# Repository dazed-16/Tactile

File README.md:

# Tactile

Tactile is a custom split mechanical keyboard for programming, live coding and CAD, with a thumb touchpad for pointer control.

## Why make it?

The aim is a keyboard that feels personal and comfortable during long desk sessions. A split layout lets each hand rest at its own angle, while thumb controls reduce trips between the keyboard and mouse. Tactile switches give clear feedback, and printed keycaps and a case leave room for customization.

## How it works

A wireless controller connects to the computer over Bluetooth. A ribbon cable joins the two halves, and the controller scans the key matrix. The right thumb controls the touchpad; left-thumb keys handle mouse clicks. Layers provide the remaining keyboard functions.

## Challenges so far

Fitting the thumb keys and touchpad into a useful layout has meant balancing comfort with space for the electronics. Another challenge has been choosing a controller and expanding its pins to handle both the keyboard and pointing device. Matching component footprints and keeping the parts affordable still need attention.

The project is in the design stage. The boards and schematics are present; firmware and the physical build are still ahead.

## Design pictures

## Files

Open the left and right projects under `Tactile/PCB/` in KiCad. Custom libraries are in `Tactile/Libraries/`, and printable geometry is in `Tactile/Model/`. The purchase list is also available as [BOM.csv](BOM.csv).

Gerbers and drill files are in the [left fabrication folder](Tactile/PCB/Left%20side/fabrication/) and [right fabrication folder](Tactile/PCB/Right%20side/fabrication/), with a ZIP package for each half. These are design exports; fabrication checks are still pending.

## Purchase BOM

Submission estimate in USD, using the current supplier list and delivery to Mexico. Prices are per listed purchase unit; line totals already include quantity. **Estimated order total: $211.80** ($76.80 components + $95.00 shipping + $40.00 tax/import allowance).

| Component or charge | Buy quantity | Unit USD | Line total USD | Source |
| --- | --- | --- | --- | --- |
| BLE controller | 1 | 9.90 | 9.90 | [Part](https://www.seeedstudio.com/Seeed-XIAO-BLE-nRF52840-p-5201.html) |
| Tactile switches | 2 packs | 9.99 | 19.98 | [Part](https://en.akkogear.com/product/creamy-purple-u1-switch/) |
| Touchpad | 1 | 9.63 | 9.63 | [Part](https://www.mouser.com/en/ProductDetail/Cirque/TM040040-2024-302?qs=wd5RIQLrsJgMzmw571gvDw%3D%3D) |
| Matrix diodes | 100 | 0.0665 | 6.65 | [Part](https://www.digikey.com/en/products/detail/diodes-incorporated/1N4148W-7-F/815280) |
| Shift registers | 2 | 0.30 | 0.60 | [Part](https://www.digikey.com/en/products/detail/nexperia-usa-inc/74HC595D-118/763394) |
| Capacitors | 10 | 0.098 | 0.98 | [Part](https://www.digikey.com/en/products/detail/yageo/CC0805KRX7R9BB104/302874) |
| Touchpad connector | 1 | 2.00 | 2.00 | [Part](https://www.digikey.com/en/products/detail/hirose-electric-co-ltd/FH12-12S-0-5SH-55/1110316) |
| Touchpad cable (estimate) | 1 | 2.00 | 2.00 | [Part](https://www.digikey.com/en/products/detail/assmann-wsw-components/AFFC-050-12-051-11/6570261) |
| Ribbon cable | 2 feet | 1.79 | 3.58 | [Part](https://www.digikey.com/en/products/detail/assmann-wsw-components/AWG28-14-F-300/655738) |
| IDC sockets | 2 | 0.60 | 1.20 | [Part](https://www.digikey.com/en/products/detail/assmann-wsw-components/AWP-14-8240-T/5244612) |
| IDC strain reliefs | 2 | 0.10 | 0.20 | [Part](https://www.digikey.com/en/products/base-product/assmann-wsw-components/123/AWZ/567962) |
| IDC headers | 2 | 0.63 | 1.26 | [Part](https://www.digikey.com/en/products/detail/assmann-wsw-components/AWHW-14G-0202-T/5224931) |
| Power switch | 1 | 0.72 | 0.72 | [Part](https://www.digikey.com/en/products/detail/e-switch/EG1218/101726) |
| Battery | 1 | 9.95 | 9.95 | [Part](https://www.digikey.com/en/products/detail/adafruit-industries-llc/258/5054544) |
| USB cable | 1 | 4.95 | 4.95 | [Part](https://www.adafruit.com/product/4474) |
| Battery protection IC (estimate) | 1 | 1.00 | 1.00 | [Part](https://www.ti.com/product/BQ2970) |
| Dual MOSFET (estimate) | 1 | 1.50 | 1.50 | [Part](https://www.ti.com/product/CSD83325L) |
| 330 ohm resistor (estimate) | 1 | 0.10 | 0.10 | To select |
| 2.2 kOhm resistor (estimate) | 1 | 0.10 | 0.10 | To select |
| Battery connector (estimate) | 1 | 0.50 | 0.50 | [Part](https://www.jst-mfg.com/product/index.php?series=ACH) |
| DigiKey shipping | 1 | 30.00 | 30.00 | [Part](https://www.digikey.com.mx/en) |
| Seeed shipping (estimate) | 1 | 10.00 | 10.00 | [Part](https://support.seeedstudio.com/knowledgebase/topics/56172-shipping) |
| Akko shipping (estimate) | 1 | 15.00 | 15.00 | [Part](https://en.akkogear.com/faq/how-many-days-will-the-delivery-take-if-i-order-today/) |
| Mouser shipping (estimate) | 1 | 20.00 | 20.00 | [Part](https://www.mouser.mx/es/saleterms/) |
| Adafruit shipping (estimate) | 1 | 20.00 | 20.00 | [Part](https://www.adafruit.com/shippinginfo) |
| Tax and import charges (estimate) | 1 | 40.00 | 40.00 | [Part](https://wwwmatnp.sat.gob.mx/articulo/43379/articulo-27) |

The unquoted components and shipping use planning allowances, not supplier quotes. Shipping assumes separate orders from DigiKey, Seeed, Akko, Mouser and Adafruit. DigiKey's $30 follows its published Mexico rate below $100; the remaining shipping allowances are provisional. The $40 tax/import allowance is a budget reserve, not a tax-rate calculation or guaranteed upper bound. Final checkout and carrier charges may differ.

Verified diode price: **100 × $0.06650 = $6.65**, cut tape. Other listed component prices are earlier supplier estimates. No parts order has been placed.

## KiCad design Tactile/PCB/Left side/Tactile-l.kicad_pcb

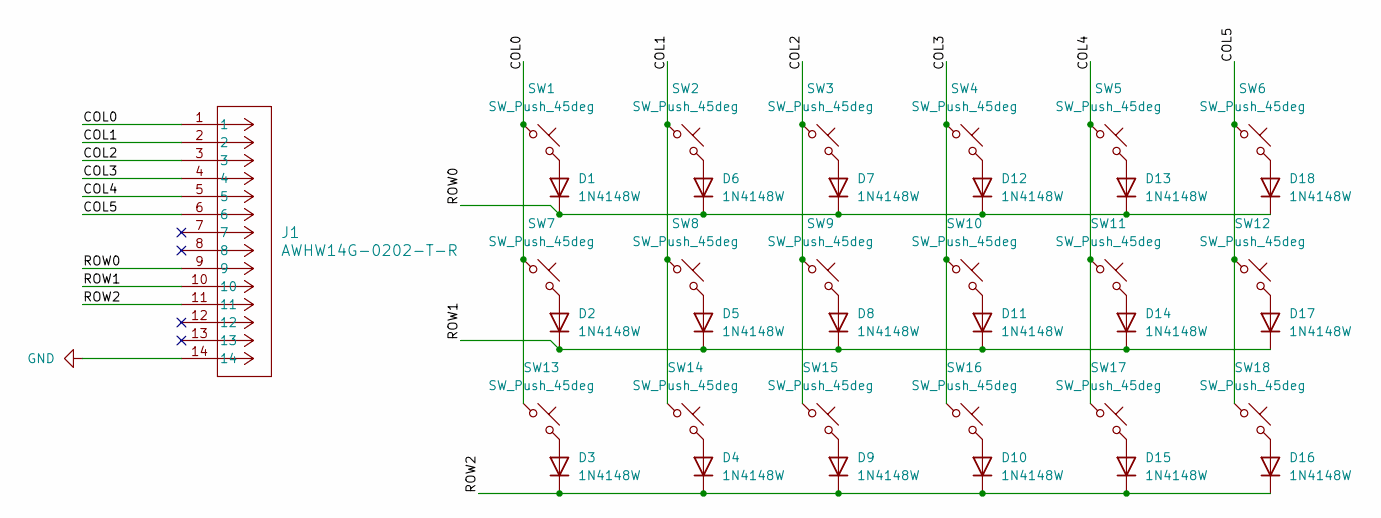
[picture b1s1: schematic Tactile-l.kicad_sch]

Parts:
D1, D2, D3, D4, D5, D6, D7, D8, D9, D10, D11, D12, D13, D14, D15, D16, D17, D18: 1N4148W; D_SOD-123
J1: AWHW14G-0202-T-R; CONN_AWHW14G-0x02-T_ASM
SW1, SW2, SW3, SW4, SW5, SW6, SW7, SW8, SW9, SW10, SW11, SW12, SW13, SW14, SW15, SW16, SW17, SW18: SW_Push_45deg; Knowles_SPH0645LM4H-6_3.5x2.65mm

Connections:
/COL0: J1.1, SW1.1, SW7.1, SW13.1
/COL1: J1.2, SW2.1, SW8.1, SW14.1
/COL2: J1.3, SW3.1, SW9.1, SW15.1
/COL3: J1.4, SW4.1, SW10.1, SW16.1
/COL4: J1.5, SW5.1, SW11.1, SW17.1
/COL5: J1.6, SW6.1, SW12.1, SW18.1
/ROW0: D1.1 (K), D6.1 (K), D7.1 (K), D12.1 (K), D13.1 (K), D18.1 (K), J1.9
/ROW1: D2.1 (K), D5.1 (K), D8.1 (K), D11.1 (K), D14.1 (K), D17.1 (K), J1.10
/ROW2: D3.1 (K), D4.1 (K), D9.1 (K), D10.1 (K), D15.1 (K), D16.1 (K), J1.11
GND: J1.14
unnamed: D1.2 (A), SW1.2
unnamed: D2.2 (A), SW7.2
unnamed: D3.2 (A), SW13.2
unnamed: D4.2 (A), SW14.2
unnamed: D5.2 (A), SW8.2
unnamed: D6.2 (A), SW2.2
unnamed: D7.2 (A), SW3.2
unnamed: D8.2 (A), SW9.2
unnamed: D9.2 (A), SW15.2
unnamed: D10.2 (A), SW16.2
unnamed: D11.2 (A), SW10.2
unnamed: D12.2 (A), SW4.2
unnamed: D13.2 (A), SW5.2
unnamed: D14.2 (A), SW11.2
unnamed: D15.2 (A), SW17.2
unnamed: D16.2 (A), SW18.2
unnamed: D17.2 (A), SW12.2
unnamed: D18.2 (A), SW6.2

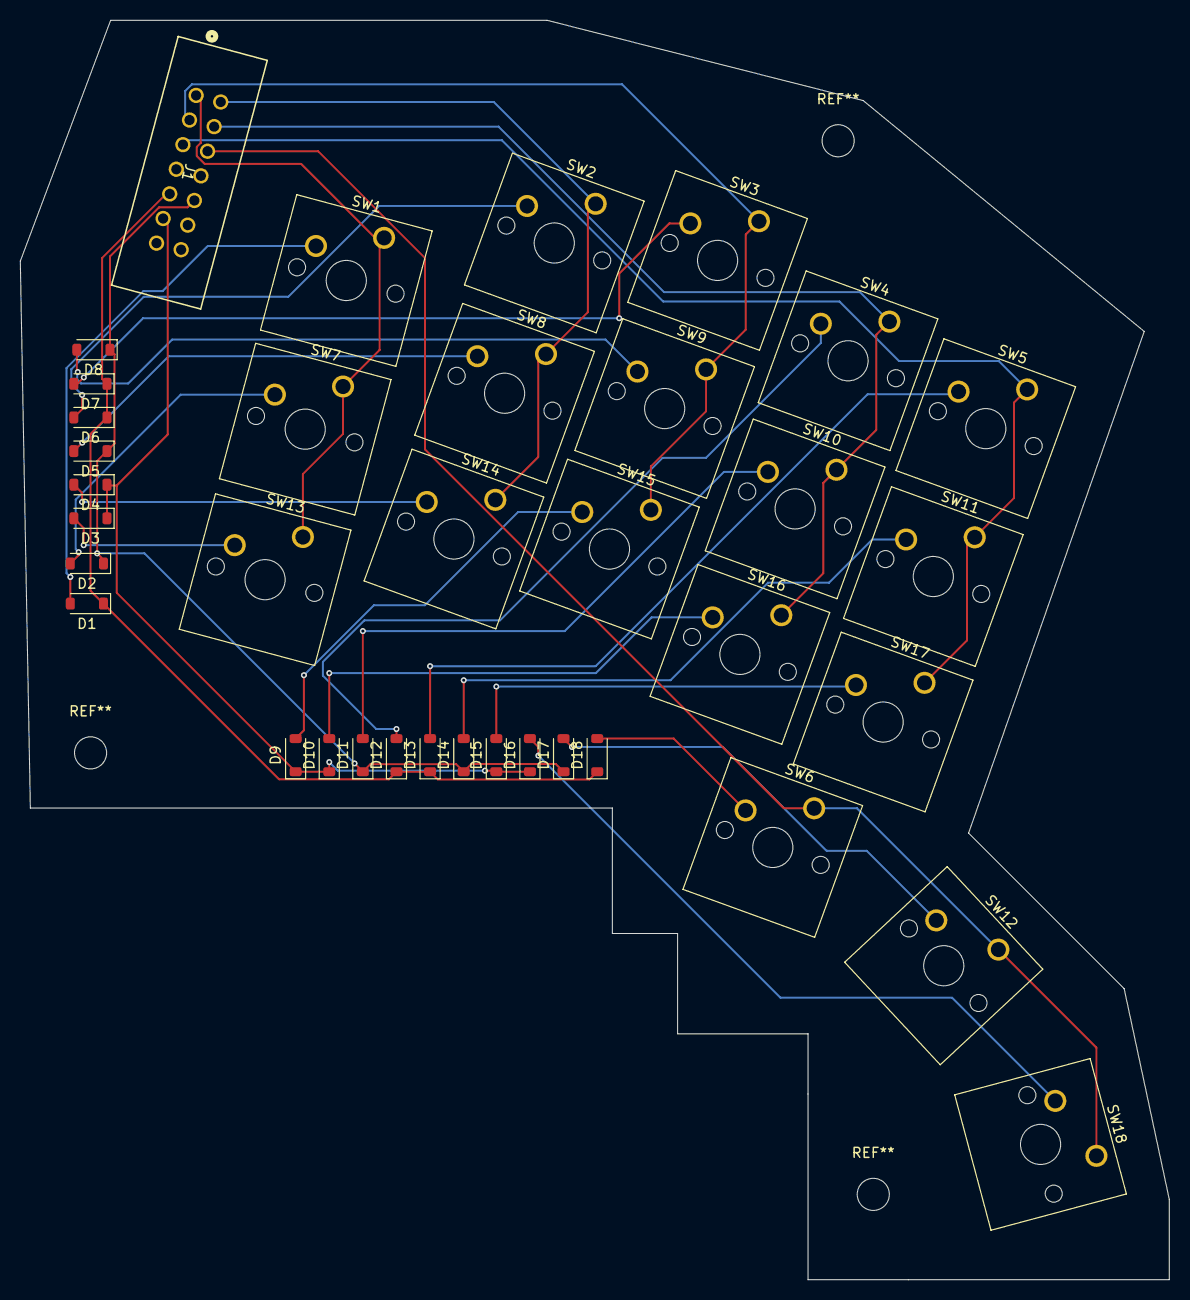
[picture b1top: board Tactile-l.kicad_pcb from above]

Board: 2 copper layers, 114.5 x 125.5 mm, 37 parts (0 on the bottom side), 27 nets.

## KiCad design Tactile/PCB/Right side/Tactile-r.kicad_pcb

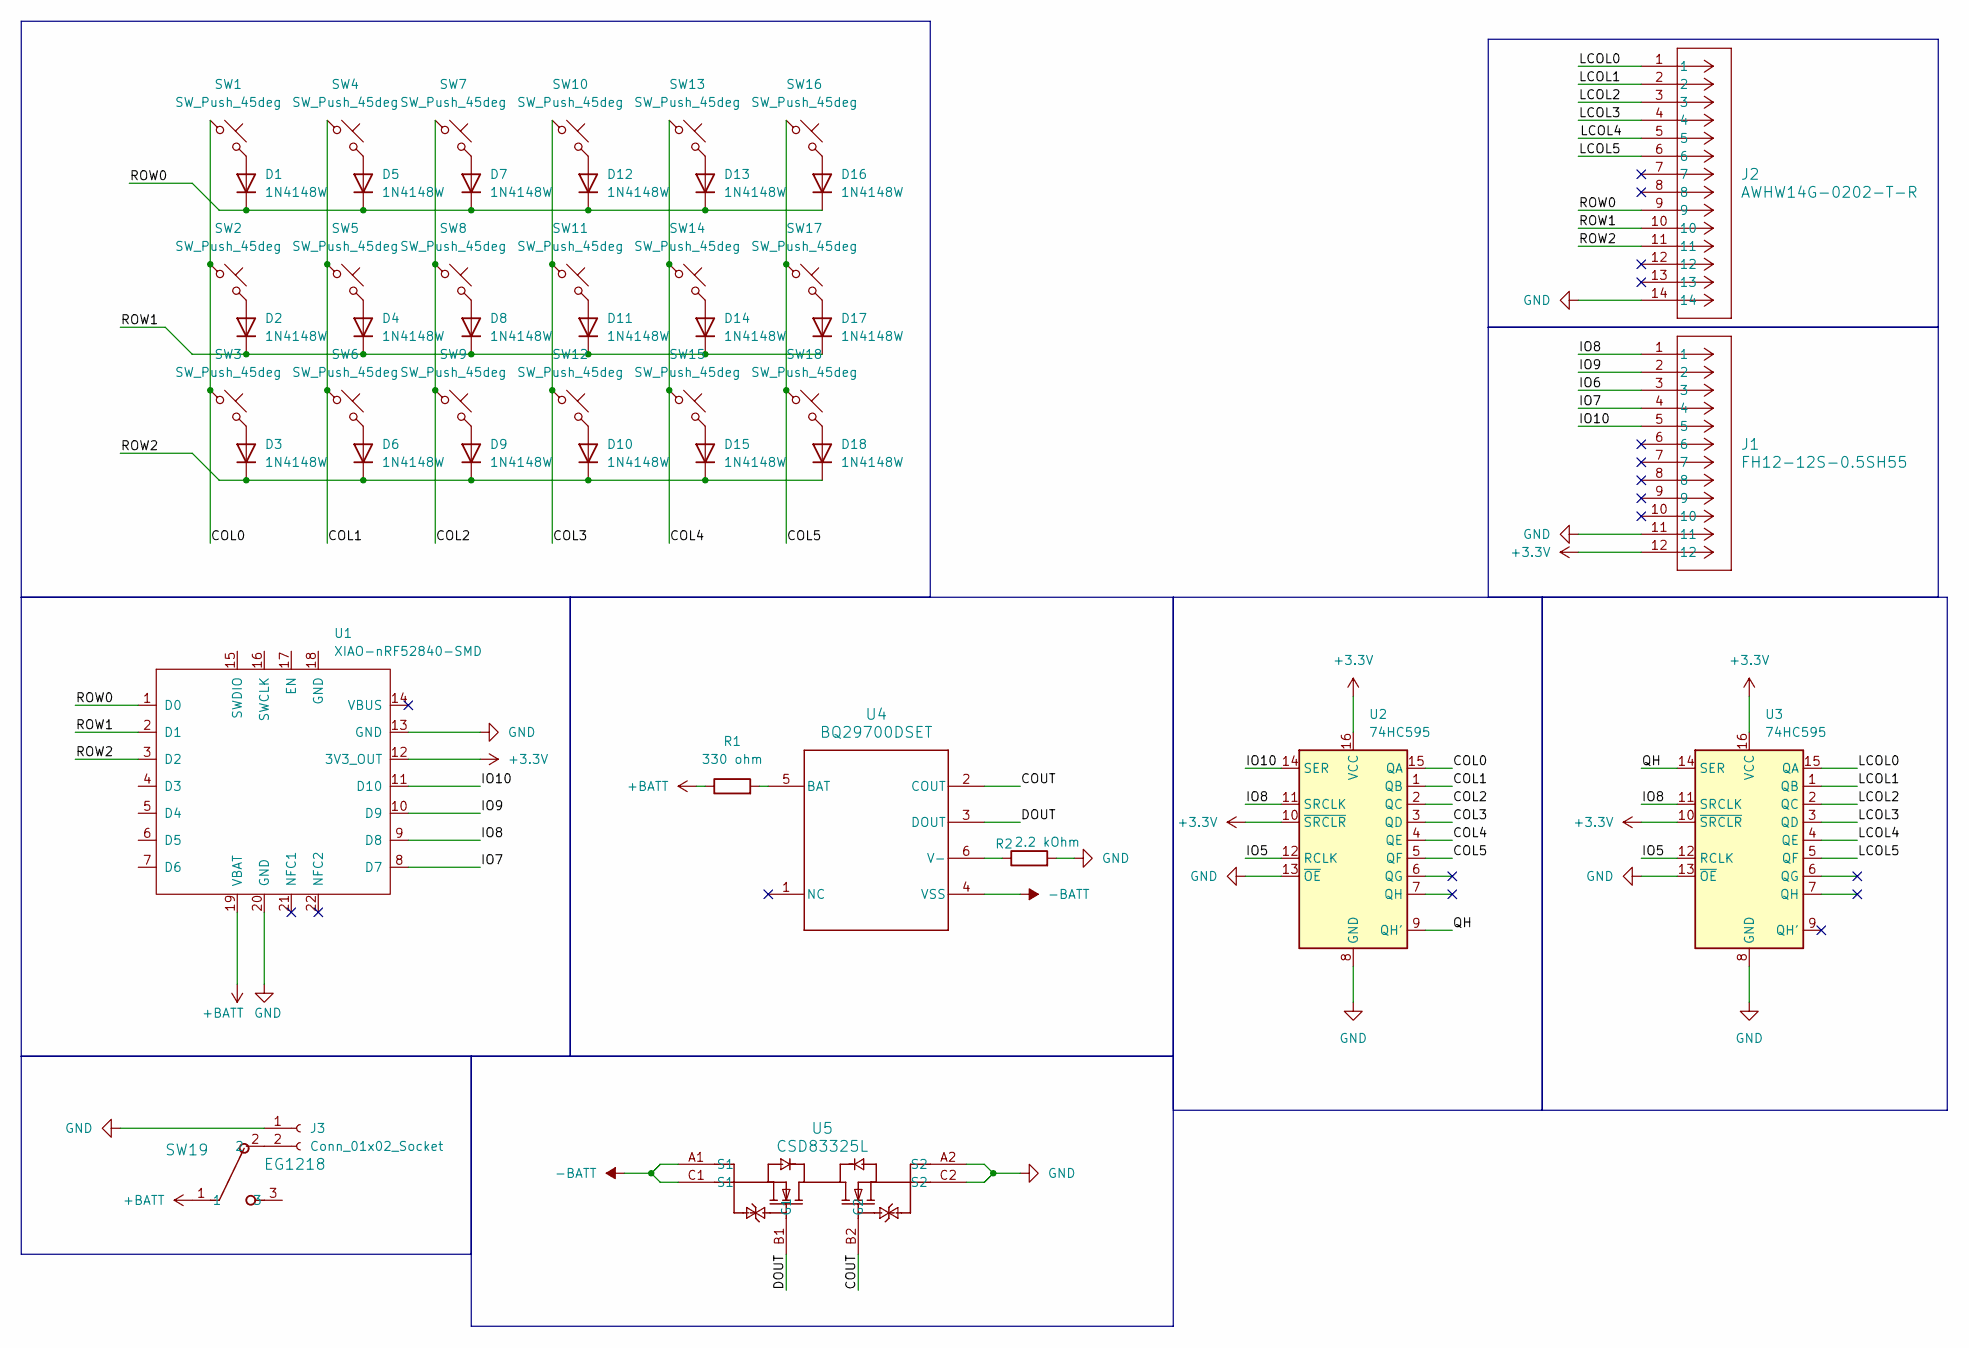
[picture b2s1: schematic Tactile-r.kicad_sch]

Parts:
D1, D2, D3, D4, D5, D6, D7, D8, D9, D10, D11, D12, D13, D14, D15, D16, D17, D18: 1N4148W; D_SOD-123
J1: FH12-12S-0.5SH55; CONN_FH12-12S-0.5SH55_HIR
J2: AWHW14G-0202-T-R; CONN_AWHW14G-0x02-T_ASM
J3: Conn_01x02_Socket; JST_ACH_BM02B-ACHSS-GAN-ETF_1x02-1MP_P1.20mm_Vertical
R1: 330 ohm; R_0603_1608Metric
R2: 2.2 kOhm; R_0603_1608Metric
SW1, SW2, SW3, SW4, SW5, SW6, SW7, SW8, SW9, SW10, SW11, SW12, SW13, SW14, SW15, SW16, SW17, SW18: SW_Push_45deg; SW_Cherry_MX_1.00u_PCB
SW19: EG1218; SW_1218_EWI
U1: XIAO-nRF52840-SMD; XIAO-nRF54LM20A-SMD
U2, U3: 74HC595; SSOP-16_5.3x6.2mm_P0.65mm
U4: BQ29700DSET; DSE0006A
U5: CSD83325L; YJE0006A

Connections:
+3.3V: J1.12, U1.12 (3V3_OUT), U2.10 (~SRCLR), U2.16 (VCC), U3.10 (~SRCLR), U3.16 (VCC)
+BATT: R1.1, SW19.1, U1.19 (VBAT)
-BATT: U4.4 (VSS), U5.A1 (S1), U5.C1 (S1)
/<NO NET>: J2.3, U3.2 (QC)
/COL0: SW1.1, SW2.1, SW3.1, U2.15 (QA)
/COL1: SW4.1, SW5.1, SW6.1, U2.1 (QB)
/COL2: SW7.1, SW8.1, SW9.1, U2.2 (QC)
/COL3: SW10.1, SW11.1, SW12.1, U2.3 (QD)
/COL4: SW13.1, SW14.1, SW15.1, U2.4 (QE)
/COL5: SW16.1, SW17.1, SW18.1, U2.5 (QF)
/COUT: U4.2 (COUT), U5.B2 (G2)
/DOUT: U4.3 (DOUT), U5.B1 (G1)
/IO5: U2.12 (RCLK), U3.12 (RCLK)
/IO6: J1.3
/IO7: J1.4, U1.8 (D7)
/IO8: J1.1, U1.9 (D8), U2.11 (SRCLK), U3.11 (SRCLK)
/IO9: J1.2, U1.10 (D9)
/IO10: J1.5, U1.11 (D10), U2.14 (SER)
/LCOL0: J2.1, U3.15 (QA)
/LCOL1: J2.2, U3.1 (QB)
/LCOL3: J2.4, U3.3 (QD)
/LCOL4: J2.5, U3.4 (QE)
/LCOL5: J2.6, U3.5 (QF)
/QH: U2.9 (QH'), U3.14 (SER)
/ROW0: D1.1 (K), D5.1 (K), D7.1 (K), D12.1 (K), D13.1 (K), D16.1 (K), J2.9, U1.1 (D0)
/ROW1: D2.1 (K), D4.1 (K), D8.1 (K), D11.1 (K), D14.1 (K), D17.1 (K), J2.10, U1.2 (D1)
/ROW2: D3.1 (K), D6.1 (K), D9.1 (K), D10.1 (K), D15.1 (K), D18.1 (K), J2.11, U1.3 (D2)
GND: J1.11, J2.14, J3.1, R2.2, U1.13 (GND), U1.20 (GND), U2.8 (GND), U2.13 (~OE), U3.8 (GND), U3.13 (~OE), U5.A2 (S2), U5.C2 (S2)
unnamed: D1.2 (A), SW1.2
unnamed: D2.2 (A), SW2.2
unnamed: D3.2 (A), SW3.2
unnamed: D4.2 (A), SW5.2
unnamed: D5.2 (A), SW4.2
unnamed: D6.2 (A), SW6.2
unnamed: D7.2 (A), SW7.2
unnamed: D8.2 (A), SW8.2
unnamed: D9.2 (A), SW9.2
unnamed: D10.2 (A), SW12.2
unnamed: D11.2 (A), SW11.2
unnamed: D12.2 (A), SW10.2
unnamed: D13.2 (A), SW13.2
unnamed: D14.2 (A), SW14.2
unnamed: D15.2 (A), SW15.2
unnamed: D16.2 (A), SW16.2
unnamed: D17.2 (A), SW17.2
unnamed: D18.2 (A), SW18.2
unnamed: J3.2, SW19.2
unnamed: R1.2, U4.5 (BAT)
unnamed: R2.1, U4.6 (V-)

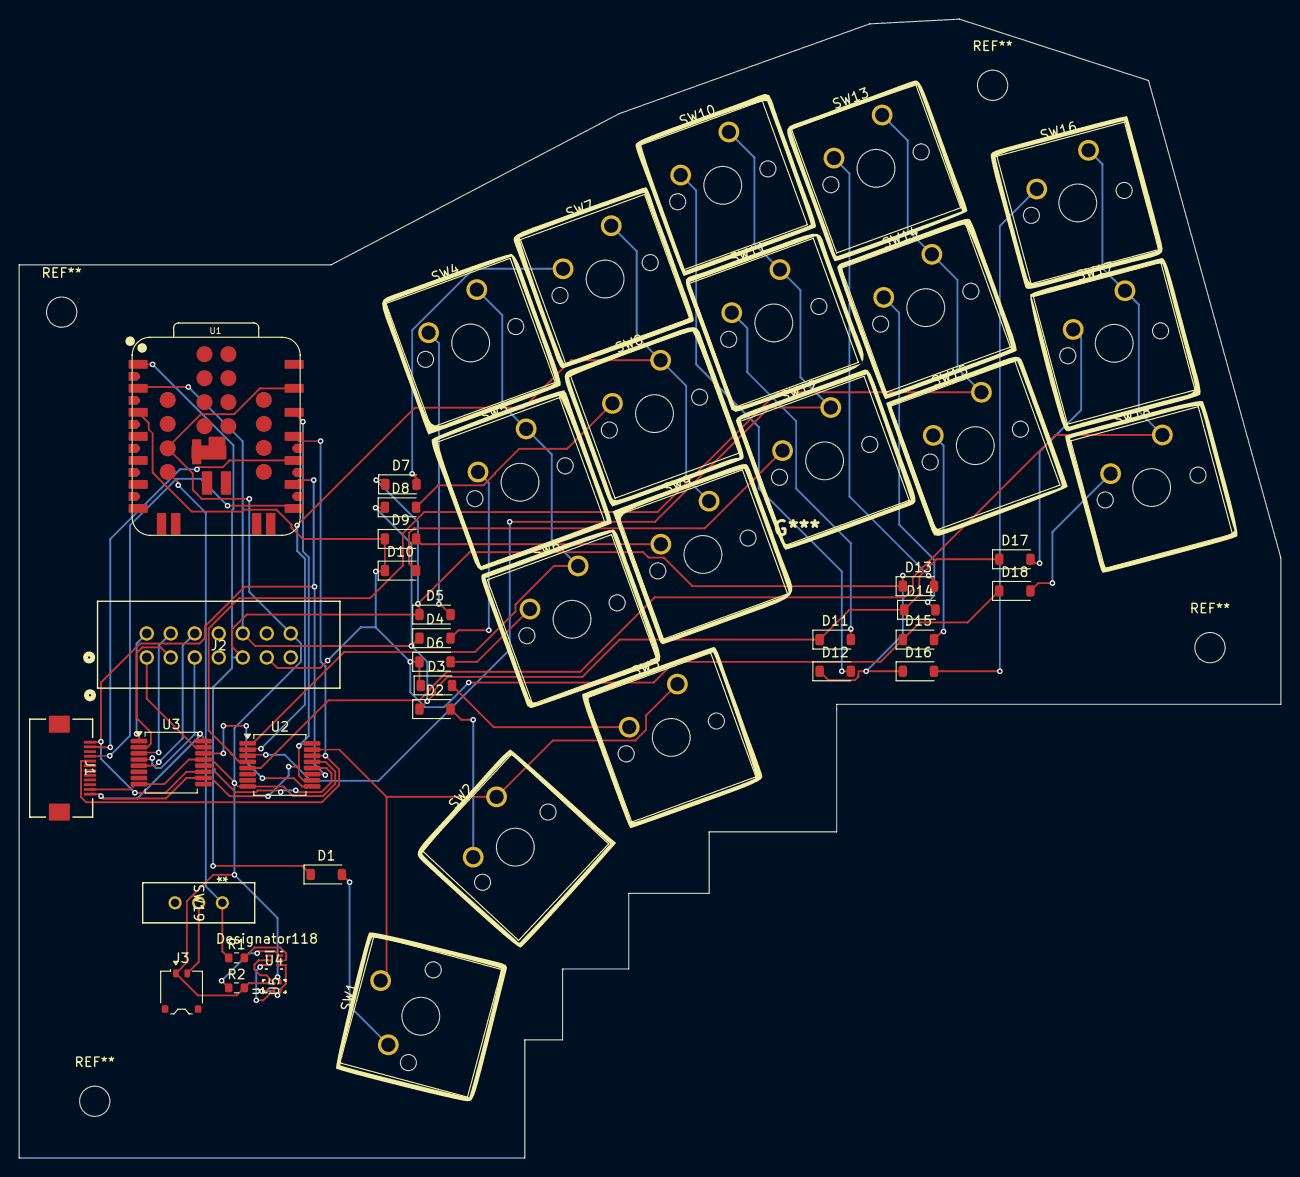
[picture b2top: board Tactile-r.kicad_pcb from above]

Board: 2 copper layers, 133.5 x 120.5 mm, 47 parts (0 on the bottom side), 48 nets.

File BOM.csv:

Item,Part,Quantity,Price USD,Link
BLE controller,102010448,1,9.90,https://www.seeedstudio.com/Seeed-XIAO-BLE-nRF52840-p-5201.html
Tactile switches,Creamy Purple U1,2 packs,19.98,https://en.akkogear.com/product/creamy-purple-u1-switch/
Touchpad,TM040040-2024-302,1,9.63,https://www.mouser.com/en/ProductDetail/Cirque/TM040040-2024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
Matrix diodes,1N4148W-7-F,100,6.65,https://www.digikey.com/en/products/detail/diodes-incorporat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
Shift registers,"74HC595D,118",2,0.60,https://www.digikey.com/en/products/detail/nexperia-usa-inc/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
Capacitors,CC0805KRX7R9BB104,10,0.98,https://www.digikey.com/en/products/detail/yageo/CC0805KRX7R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
Touchpad connector,FH12-12S-0.5SH(55),1,2.00,https://www.digikey.com/en/products/detail/hirose-electric-c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
Touchpad cable,AFFC-050-12-051-11,1,TBD,https://www.digikey.com/en/products/detail/assmann-wsw-compo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
Ribbon cable,AWG28-14/F/300,2 feet,3.58,https://www.digikey.com/en/products/detail/assmann-wsw-compo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
IDC sockets,AWP 14-8240-T,2,1.20,https://www.digikey.com/en/products/detail/assmann-wsw-compo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
IDC strain reliefs,AWZ-14-T,2,0.20,https://www.digikey.com/en/products/base-product/assmann-wsw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
IDC headers,AWHW 14G-0202-T,2,1.26,https://www.digikey.com/en/products/detail/assmann-wsw-compo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
Power switch,EG1218,1,0.72,https://www.digikey.com/en/products/detail/e-switch/EG1218/101726
Battery,258,1,9.95,https://www.digikey.com/en/products/detail/adafruit-industri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
USB cable,4474,1,4.95,https://www.adafruit.com/product/4474
Battery protection IC,BQ29700DSET,1,TBD,https://www.ti.com/product/BQ2970
Dual MOSFET,CSD83325L,1,TBD,https://www.ti.com/product/CSD83325L
330 ohm resistor,TBD; 0603,1,TBD,TBD
2.2 kOhm resistor,TBD; 0603,1,TBD,TBD
Battery connector,BM02B-ACHSS-GAN-ETF,1,TBD,https://www.jst-mfg.com/product/index.php?series=ACH
